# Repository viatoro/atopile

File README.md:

<h1 align="center">
    <picture>
    <source media="(prefers-color-scheme: dark)" srcset="https://github.com/atopile/atopile/assets/9785003/00f19584-18a2-4b5f-9ce4-1248798974dd">
    <source media="(prefers-color-scheme: light)" src="https://github.com/atopile/atopile/assets/9785003/d38941c1-d7c1-42e6-9b94-a62a0996bc19">
    
    </picture>
</h1>

<p align="center">

</p>

## Design circuit boards with code

Write hardware like software. atopile is a language, compiler, and toolchain for electronics—declarative `.ato` files, deep validation, and layout that works natively with KiCad.

## Why atopile

- Reusable modules instead of starting from scratch every time
- Capture intent with equations directly in your design
- Automatic parametric picking of discrete components

## Install

The easiest way is via the editor extension—it installs and manages `ato` for you:

- VS Code/Cursor extension: https://marketplace.visualstudio.com/items?itemName=atopile.atopile

Advanced setups and CLI installs: https://docs.atopile.io/atopile/guides/install

## Quickstart (2 minutes)

1. Install the extension (link above)

2. In the editor, run “atopile: Open Example” and pick one

3. Press the ▶ in the ato menu bar to build, or run `ato build` from the terminal

4. Open layout when ready

Notes:

- The ato menu bar is in the bottom-left of your VS Code/Cursor window
- KiCad is optional to get started. Without it, you won’t open the PCB, but builds still run and update the `.kicad_pcb`. Install later when you’re ready for layout: https://docs.atopile.io/atopile/quickstart

## How it works

- `ato` is a declarative language for electronics: modules, interfaces, units, tolerances, and assertions
- The compiler solves constraints, picks parts, runs checks, and updates your KiCad layout
- The extension adds language services and one‑click controls

Learn more: https://docs.atopile.io/atopile/essentials/1-the-ato-language

### Where atopile fits in

High-level steps:

- Requirements — capture specs with units, tolerances, and assertions
- Component selection — parametric picking, reuse proven modules
- Design capture — `.ato` modules and interfaces compose your system
- Layout — place and route in KiCad
- Checks — run design checks locally or in CI
- Build outputs — BOM, fabrication and assembly data, reports
- PCB fab/assembly — send outputs to your manufacturer

## Example Projects

- Open examples via the editor (“atopile: Open Example”) https://github.com/atopile/atopile/tree/main/examples
- NONOS — Open-source smart speaker https://github.com/atopile/nonos
- DSP - Open-source multi-channel DSP https://github.com/atopile/dsp
- AI-Pin — Vibe-coded Humane Pin https://github.com/atopile/ai-pin
- Hyperion — 300K nit display for raves https://github.com/atopile/hyperion
- Cellsim - 18 channel battery cell simulator https://github.com/atopile/cellsim
- ESPaper - ESP32 epaper display driver https://github.com/atopile/hivehaus/tree/master/src/products/espaper

## Packages and parts

- Browse and install modules from the registry: https://packages.atopile.io
- Guide: https://docs.atopile.io/atopile/essentials/4-packages
- Publish your own: https://docs.atopile.io/atopile/guides/publish

## Compatibility

- OS: macOS, Linux, Windows (WSL recommended)
- Recommended editors: VS Code / Cursor
- EDA: KiCad recommended for layout; not required to start

## Contributing and development

- Development setup: https://docs.atopile.io/atopile/guides/development
- Editable install (for working on atopile itself): https://docs.atopile.io/atopile/guides/install#editable-installation-best-for-development
- Run tests:

```sh
pytest -q
```

- Fast worktree setup (CoW-clone `.venv` + Zig cache/output, then path rewrite):

```sh
ato dev worktree <suffix>
cd ../atopile_<suffix>
source .venv/bin/activate
ato --help
```

By default this command starts an interactive shell in the new worktree.
Pass `--no-cd` to skip shell handoff.

- Issues and feature requests: https://github.com/atopile/atopile/issues

## Support

- Discord “help” channel: https://discord.gg/CRe5xaDBr3
- Commercial support: hi@atopile.io

## License

MIT. See `LICENSE`.

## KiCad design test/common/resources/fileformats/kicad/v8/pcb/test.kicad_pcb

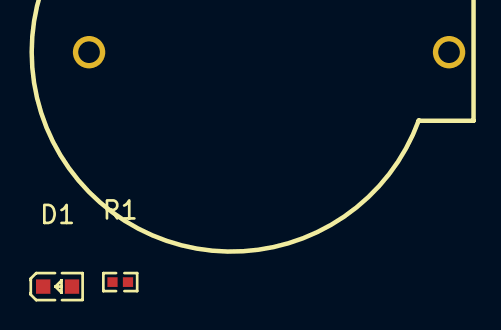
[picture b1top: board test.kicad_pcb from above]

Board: 2 copper layers, 3 parts (0 on the bottom side), 3 nets, no tracks yet.

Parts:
B1: ButtonCell; BAT-TH_BS-02-A1AJ010
D1: LED; LED0603-RD-YELLOW
R1: 40.2Ω; R0402

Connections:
B1-1-R1-2: B1.1, R1.2
B1-2-D1-2: B1.2, D1.2
D1-1-R1-1: D1.1, R1.1

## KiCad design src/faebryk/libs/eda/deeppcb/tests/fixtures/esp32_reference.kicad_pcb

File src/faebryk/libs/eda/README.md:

# faebryk.libs.eda

Shared EDA package layout.

The common layering is:

```text
file -> ll -> il -> hl

file  = on-disk format / parser-writer boundary
ll    = low-level, format-shaped model
il    = intermediate semantic model for one EDA
hl    = shared atopile-facing connectivity model
```

## Per-EDA Flow

```text
Altium PCB / schematic
----------------------
.PcbDoc / .SchDoc
    -> convert/*/file_ll.py
    -> models/*/ll.py
    -> convert/*/il_ll.py
    -> models/*/il.py
    -> convert/*/il_hl.py
    -> hl/models/*.py
    -> hl/convert/*.py
    -> Netlist
```

```text
KiCad PCB / schematic
---------------------
.kicad_pcb / .kicad_sch
    -> faebryk.libs.kicad.fileformats
    -> pyzig KiCad AST / IL
    -> eda/kicad/convert/*/il_hl.py
    -> hl/models/*.py
    -> hl/convert/*.py
    -> Netlist
```

## Intent

- Keep each EDA-specific format separate.
- Keep `hl/` EDA-agnostic.
- Make `il -> hl` the bridge into shared atopile connectivity logic.
- Preserve room for both directions later:
  `file <-> ll <-> il <-> hl`

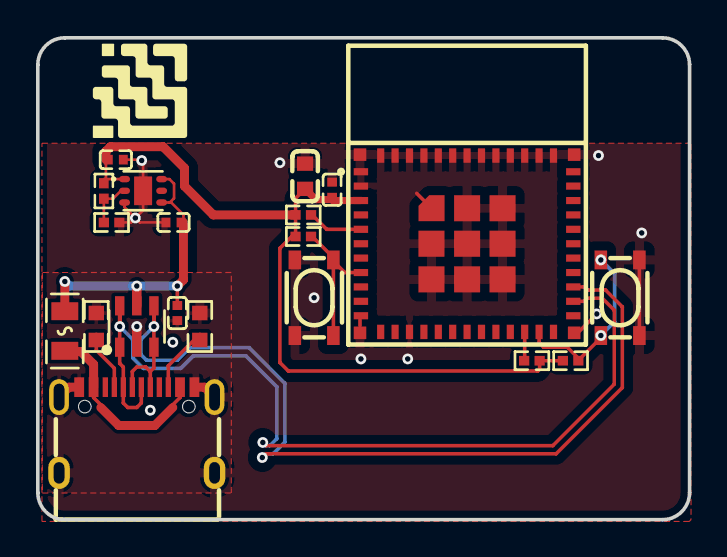
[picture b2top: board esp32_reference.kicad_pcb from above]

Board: 2 copper layers, 36.2 x 26.8 mm, 20 parts (0 on the bottom side), 13 nets.

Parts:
C1, C2: 1µF ±10%; C0402
C3, C5: 100nF ±10%; C0402
C4: 22µF ±20%; C0603
D1: SOT-23-6_L2.9-W1.6-P0.95-LS2.8-BL
F1: F0805
R1: 9.09kΩ ±1%; R0402
R2: 1.82kΩ ±1%; R0402
R3, R4, R8: 10kΩ ±1%; R0402
R5: 5.1kΩ ±1%; R0402
R6, R7: 10kΩ ±1%; R0603
SW1, SW2: KEY-SMD_4P-L4.2-W3.2-P2.20-LS4.6
U1: WIFIM-SMD_ESP32-C3-MINI-1
U3: WSON-6_L2.0-W2.0-P0.65-TL-EP
USB1: USB-C-SMD_TYPE-C-6PIN-2MD-073

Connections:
4: R6.1, USB1.4
10: R7.1, USB1.10
DATA_1: R3.1, U1.5
DATA_N: D1.1, D1.6, U1.26, USB1.5, USB1.7
DATA_P: D1.3, D1.4, U1.27, USB1.6, USB1.8
MISO: R4.1, U1.22
N_TRST: R8.2, SW2.3, SW2.4, U1.8
hv: C1.1, C3.1, D1.5, F1.2, U3.4, U3.6
lv: C1.2, C2.2, C3.2, C4.2, C5.2, D1.2, R2.2, R6.2, R7.2, SW1.1, SW1.2, SW2.1, SW2.2, U1.1, U1.2, U1.11, U1.14, U1.36, U1.37, U1.38, U1.39, U1.40, U1.41, U1.42, U1.43, U1.44, U1.45, U1.46, U1.47, U1.48, U1.49, U1.50, U1.51, U1.52, U1.53, U3.3, U3.7, USB1.1, USB1.12, USB1.13, USB1.14, USB1.15, USB1.16
output: R5.2, SW1.3, SW1.4, U1.23
power-hv: C2.1, C4.1, C5.1, R1.1, R3.2, R4.2, R5.1, R8.1, U1.3, U3.1
power_vbus-hv: F1.1, USB1.2, USB1.11
ref_out-hv: R1.2, R2.1, U3.2

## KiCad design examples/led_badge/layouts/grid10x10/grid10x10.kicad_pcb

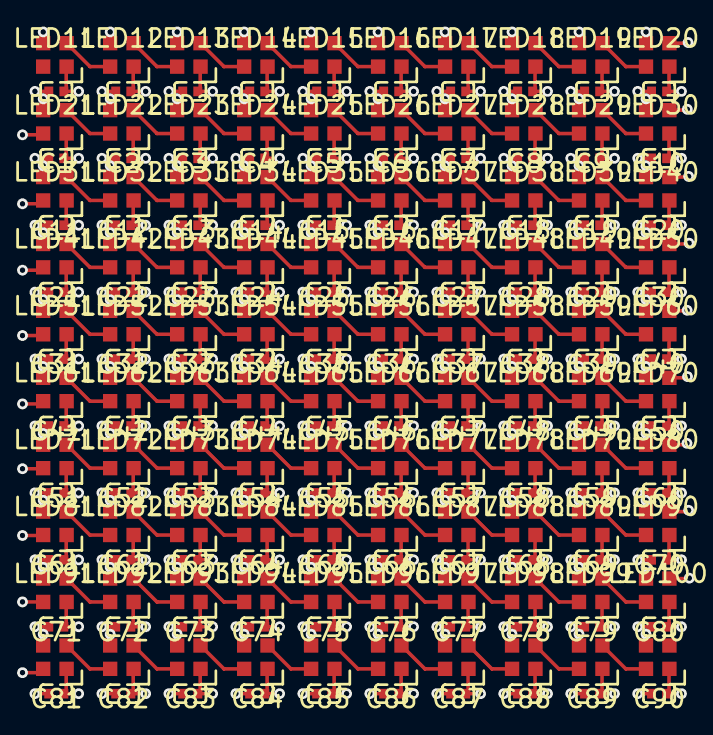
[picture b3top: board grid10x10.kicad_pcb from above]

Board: 4 copper layers, 200 parts (0 on the bottom side), 101 nets.

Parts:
C1, C2, C3, C4, C5, C6, C7, C8, C9, C10, C11, C12, C13, C14, C15, C16, C17, C18, C19, C20, C21, C22, C23, C24, C25, C26, C27, C28, C29, C30, C31, C32, C33, C34, C35, C36, C37, C38, C39, C40, C41, C42, C43, C44, C45, C46, C47, C48, C49, C50, C51, C52, C53, C54, C55, C56, C57, C58, C59, C60, C61, C62, C63, C64, C65, C66, C67, C68, C69, C70, C71, C72, C73, C74, C75, C76, C77, C78, C79, C80, C81, C82, C83, C84, C85, C86, C87, C88, C89, C90, C91, C92, C93, C94, C95, C96, C97, C98, C99, C100: 100nF ±10%; C0402
LED1, LED2, LED3, LED4, LED5, LED6, LED7, LED8, LED9, LED10, LED11, LED12, LED13, LED14, LED15, LED16, LED17, LED18, LED19, LED20, LED21, LED22, LED23, LED24, LED25, LED26, LED27, LED28, LED29, LED30, LED31, LED32, LED33, LED34, LED35, LED36, LED37, LED38, LED39, LED40, LED41, LED42, LED43, LED44, LED45, LED46, LED47, LED48, LED49, LED50, LED51, LED52, LED53, LED54, LED55, LED56, LED57, LED58, LED59, LED60, LED61, LED62, LED63, LED64, LED65, LED66, LED67, LED68, LED69, LED70, LED71, LED72, LED73, LED74, LED75, LED76, LED77, LED78, LED79, LED80, LED81, LED82, LED83, LED84, LED85, LED86, LED87, LED88, LED89, LED90, LED91, LED92, LED93, LED94, LED95, LED96, LED97, LED98, LED99, LED100: LED-SMD_4P-L2.0-W2.0-BR

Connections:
DIN: LED1.2, LED2.4
hv: C1.1, C2.1, C3.1, C4.1, C5.1, C6.1, C7.1, C8.1, C9.1, C10.1, C11.1, C12.1, C13.1, C14.1, C15.1, C16.1, C17.1, C18.1, C19.1, C20.1, C21.1, C22.1, C23.1, C24.1, C25.1, C26.1, C27.1, C28.1, C29.1, C30.1, C31.1, C32.1, C33.1, C34.1, C35.1, C36.1, C37.1, C38.1, C39.1, C40.1, C41.1, C42.1, C43.1, C44.1, C45.1, C46.1, C47.1, C48.1, C49.1, C50.1, C51.1, C52.1, C53.1, C54.1, C55.1, C56.1, C57.1, C58.1, C59.1, C60.1, C61.1, C62.1, C63.1, C64.1, C65.1, C66.1, C67.1, C68.1, C69.1, C70.1, C71.1, C72.1, C73.1, C74.1, C75.1, C76.1, C77.1, C78.1, C79.1, C80.1, C81.1, C82.1, C83.1, C84.1, C85.1, C86.1, C87.1, C88.1, C89.1, C90.1, C91.1, C92.1, C93.1, C94.1, C95.1, C96.1, C97.1, C98.1, C99.1, C100.1, LED1.1, LED2.1, LED3.1, LED4.1, LED5.1, LED6.1, LED7.1, LED8.1, LED9.1, LED10.1, LED11.1, LED12.1, LED13.1, LED14.1, LED15.1, LED16.1, LED17.1, LED18.1, LED19.1, LED20.1, LED21.1, LED22.1, LED23.1, LED24.1, LED25.1, LED26.1, LED27.1, LED28.1, LED29.1, LED30.1, LED31.1, LED32.1, LED33.1, LED34.1, LED35.1, LED36.1, LED37.1, LED38.1, LED39.1, LED40.1, LED41.1, LED42.1, LED43.1, LED44.1, LED45.1, LED46.1, LED47.1, LED48.1, LED49.1, LED50.1, LED51.1, LED52.1, LED53.1, LED54.1, LED55.1, LED56.1, LED57.1, LED58.1, LED59.1, LED60.1, LED61.1, LED62.1, LED63.1, LED64.1, LED65.1, LED66.1, LED67.1, LED68.1, LED69.1, LED70.1, LED71.1, LED72.1, LED73.1, LED74.1, LED75.1, LED76.1, LED77.1, LED78.1, LED79.1, LED80.1, LED81.1, LED82.1, LED83.1, LED84.1, LED85.1, LED86.1, LED87.1, LED88.1, LED89.1, LED90.1, LED91.1, LED92.1, LED93.1, LED94.1, LED95.1, LED96.1, LED97.1, LED98.1, LED99.1, LED100.1
leds[1]-data_in-DIN: LED11.2, LED12.4
leds[1]-data_in-DIN-1: LED21.2, LED22.4
leds[1]-data_in-DIN-2: LED31.2, LED32.4
leds[1]-data_in-DIN-3: LED41.2, LED42.4
leds[1]-data_in-DIN-4: LED51.2, LED52.4
leds[1]-data_in-DIN-5: LED61.2, LED62.4
leds[1]-data_in-DIN-6: LED71.2, LED72.4
leds[1]-data_in-DIN-7: LED81.2, LED82.4
leds[1]-data_in-DIN-8: LED91.2, LED92.4
leds[2]-data_in-DIN: LED2.2, LED3.4
leds[2]-data_in-DIN-1: LED12.2, LED13.4
leds[2]-data_in-DIN-2: LED22.2, LED23.4
leds[2]-data_in-DIN-3: LED32.2, LED33.4
leds[2]-data_in-DIN-4: LED42.2, LED43.4
leds[2]-data_in-DIN-5: LED52.2, LED53.4
leds[2]-data_in-DIN-6: LED62.2, LED63.4
leds[2]-data_in-DIN-7: LED72.2, LED73.4
leds[2]-data_in-DIN-8: LED82.2, LED83.4
leds[2]-data_in-DIN-9: LED92.2, LED93.4
leds[3]-data_in-DIN: LED3.2, LED4.4
leds[3]-data_in-DIN-1: LED13.2, LED14.4
leds[3]-data_in-DIN-2: LED23.2, LED24.4
leds[3]-data_in-DIN-3: LED33.2, LED34.4
leds[3]-data_in-DIN-4: LED43.2, LED44.4
leds[3]-data_in-DIN-5: LED53.2, LED54.4
leds[3]-data_in-DIN-6: LED63.2, LED64.4
leds[3]-data_in-DIN-7: LED73.2, LED74.4
leds[3]-data_in-DIN-8: LED83.2, LED84.4
leds[3]-data_in-DIN-9: LED93.2, LED94.4
leds[4]-data_in-DIN: LED4.2, LED5.4
leds[4]-data_in-DIN-1: LED14.2, LED15.4
leds[4]-data_in-DIN-2: LED24.2, LED25.4
leds[4]-data_in-DIN-3: LED34.2, LED35.4
leds[4]-data_in-DIN-4: LED44.2, LED45.4
leds[4]-data_in-DIN-5: LED54.2, LED55.4
leds[4]-data_in-DIN-6: LED64.2, LED65.4
leds[4]-data_in-DIN-7: LED74.2, LED75.4
leds[4]-data_in-DIN-8: LED84.2, LED85.4
leds[4]-data_in-DIN-9: LED94.2, LED95.4
leds[5]-data_in-DIN: LED5.2, LED6.4
leds[5]-data_in-DIN-1: LED15.2, LED16.4
leds[5]-data_in-DIN-2: LED25.2, LED26.4
leds[5]-data_in-DIN-3: LED35.2, LED36.4
leds[5]-data_in-DIN-4: LED45.2, LED46.4
leds[5]-data_in-DIN-5: LED55.2, LED56.4
leds[5]-data_in-DIN-6: LED65.2, LED66.4
leds[5]-data_in-DIN-7: LED75.2, LED76.4
leds[5]-data_in-DIN-8: LED85.2, LED86.4
leds[5]-data_in-DIN-9: LED95.2, LED96.4
leds[6]-data_in-DIN: LED6.2, LED7.4
leds[6]-data_in-DIN-1: LED16.2, LED17.4
leds[6]-data_in-DIN-2: LED26.2, LED27.4
leds[6]-data_in-DIN-3: LED36.2, LED37.4
leds[6]-data_in-DIN-4: LED46.2, LED47.4
leds[6]-data_in-DIN-5: LED56.2, LED57.4
leds[6]-data_in-DIN-6: LED66.2, LED67.4
leds[6]-data_in-DIN-7: LED76.2, LED77.4
leds[6]-data_in-DIN-8: LED86.2, LED87.4
leds[6]-data_in-DIN-9: LED96.2, LED97.4
leds[7]-data_in-DIN: LED7.2, LED8.4
leds[7]-data_in-DIN-1: LED17.2, LED18.4
leds[7]-data_in-DIN-2: LED27.2, LED28.4
leds[7]-data_in-DIN-3: LED37.2, LED38.4
leds[7]-data_in-DIN-4: LED47.2, LED48.4
leds[7]-data_in-DIN-5: LED57.2, LED58.4
leds[7]-data_in-DIN-6: LED67.2, LED68.4
leds[7]-data_in-DIN-7: LED77.2, LED78.4
leds[7]-data_in-DIN-8: LED87.2, LED88.4
leds[7]-data_in-DIN-9: LED97.2, LED98.4
leds[8]-data_in-DIN: LED8.2, LED9.4
leds[8]-data_in-DIN-1: LED18.2, LED19.4
leds[8]-data_in-DIN-2: LED28.2, LED29.4
leds[8]-data_in-DIN-3: LED38.2, LED39.4
leds[8]-data_in-DIN-4: LED48.2, LED49.4
leds[8]-data_in-DIN-5: LED58.2, LED59.4
leds[8]-data_in-DIN-6: LED68.2, LED69.4
leds[8]-data_in-DIN-7: LED78.2, LED79.4
leds[8]-data_in-DIN-8: LED88.2, LED89.4
leds[8]-data_in-DIN-9: LED98.2, LED99.4
leds[9]-data_in-DIN: LED9.2, LED10.4
leds[9]-data_in-DIN-1: LED19.2, LED20.4
leds[9]-data_in-DIN-2: LED29.2, LED30.4
leds[9]-data_in-DIN-3: LED39.2, LED40.4
leds[9]-data_in-DIN-4: LED49.2, LED50.4
leds[9]-data_in-DIN-5: LED59.2, LED60.4
leds[9]-data_in-DIN-6: LED69.2, LED70.4
leds[9]-data_in-DIN-7: LED79.2, LED80.4
leds[9]-data_in-DIN-8: LED89.2, LED90.4
leds[9]-data_in-DIN-9: LED99.2, LED100.4
lv: C1.2, C2.2, C3.2, C4.2, C5.2, C6.2, C7.2, C8.2, C9.2, C10.2, C11.2, C12.2, C13.2, C14.2, C15.2, C16.2, C17.2, C18.2, C19.2, C20.2, C21.2, C22.2, C23.2, C24.2, C25.2, C26.2, C27.2, C28.2, C29.2, C30.2, C31.2, C32.2, C33.2, C34.2, C35.2, C36.2, C37.2, C38.2, C39.2, C40.2, C41.2, C42.2, C43.2, C44.2, C45.2, C46.2, C47.2, C48.2, C49.2, C50.2, C51.2, C52.2, C53.2, C54.2, C55.2, C56.2, C57.2, C58.2, C59.2, C60.2, C61.2, C62.2, C63.2, C64.2, C65.2, C66.2, C67.2, C68.2, C69.2, C70.2, C71.2, C72.2, C73.2, C74.2, C75.2, C76.2, C77.2, C78.2, C79.2, C80.2, C81.2, C82.2, C83.2, C84.2, C85.2, C86.2, C87.2, C88.2, C89.2, C90.2, C91.2, C92.2, C93.2, C94.2, C95.2, C96.2, C97.2, C98.2, C99.2, C100.2, LED1.3, LED2.3, LED3.3, LED4.3, LED5.3, LED6.3, LED7.3, LED8.3, LED9.3, LED10.3, LED11.3, LED12.3, LED13.3, LED14.3, LED15.3, LED16.3, LED17.3, LED18.3, LED19.3, LED20.3, LED21.3, LED22.3, LED23.3, LED24.3, LED25.3, LED26.3, LED27.3, LED28.3, LED29.3, LED30.3, LED31.3, LED32.3, LED33.3, LED34.3, LED35.3, LED36.3, LED37.3, LED38.3, LED39.3, LED40.3, LED41.3, LED42.3, LED43.3, LED44.3, LED45.3, LED46.3, LED47.3, LED48.3, LED49.3, LED50.3, LED51.3, LED52.3, LED53.3, LED54.3, LED55.3, LED56.3, LED57.3, LED58.3, LED59.3, LED60.3, LED61.3, LED62.3, LED63.3, LED64.3, LED65.3, LED66.3, LED67.3, LED68.3, LED69.3, LED70.3, LED71.3, LED72.3, LED73.3, LED74.3, LED75.3, LED76.3, LED77.3, LED78.3, LED79.3, LED80.3, LED81.3, LED82.3, LED83.3, LED84.3, LED85.3, LED86.3, LED87.3, LED88.3, LED89.3, LED90.3, LED91.3, LED92.3, LED93.3, LED94.3, LED95.3, LED96.3, LED97.3, LED98.3, LED99.3, LED100.3
rows[1]-data_in-line: LED10.2, LED11.4
rows[2]-data_in-line: LED20.2, LED21.4
rows[3]-data_in-line: LED30.2, LED31.4
rows[4]-data_in-line: LED40.2, LED41.4
rows[5]-data_in-line: LED50.2, LED51.4
rows[6]-data_in-line: LED60.2, LED61.4
rows[7]-data_in-line: LED70.2, LED71.4
rows[8]-data_in-line: LED80.2, LED81.4
rows[9]-data_in-line: LED90.2, LED91.4
